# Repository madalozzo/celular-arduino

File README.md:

# celular-arduino

# ATENÇAO - GIP (gambiarra in progress)

Este projeto é um celular básico, do estilo dos Nokia's indestrutíveis do início do século, com a diferença que este não é indestrutível e também não tem o jogo da cobrinha. A idéia é um celular que receba e faça chamadas, receba e envie SMS.

# Peças:

- https://www.adafruit.com/product/1946 
- https://www.arduino.cc/en/pmwiki.php?n=Main/ArduinoBoardProMini de 3v3 8mhz
- https://www.sparkfun.com/products/retired/10968 não está mais a venda mas achei esse substituto: https://www.filipeflop.com/produto/conversor-boost-dc-step-up/
- https://www.filipeflop.com/produto/motor-de-vibracao-1027 o que usei não está mais a venda, este é o mais parecido e tecnicamente é compatível
- Antena GSM (achar o link)
- Alto falante (achar link)
- LCD (achar link tb)
- Bateria (link)
- Microfone (achar link tb...)
- Placa para os botões (projeto eagle neste repo)
- Design do celular (svg no repo tb)

### Desejável
- Espírito gambiarreiro.

# Arduino IDE
Você vai precisar das seguintes libs instaladas:
- Adafruit FONA Library
- Keypad do Mark Stanley
- Lib do LCD deste link https://wiki.seeedstudio.com/I2C_LCD/

# Recursos usados
<div>Icons made by <a href="https://www.flaticon.com/authors/gregor-cresnar" title="Gregor Cresnar">Gregor Cresnar</a> from <a href="https://www.flaticon.com/" title="Flaticon">www.flaticon.com</a></div>

<div>Icons made by <a href="https://www.freepik.com" title="Freepik">Freepik</a> from <a href="https://www.flaticon.com/" title="Flaticon">www.flaticon.com</a></div>

<div>Icons made by <a href="https://www.flaticon.com/authors/those-icons" title="Those Icons">Those Icons</a> from <a href="https://www.flaticon.com/" title="Flaticon">www.flaticon.com</a></div>

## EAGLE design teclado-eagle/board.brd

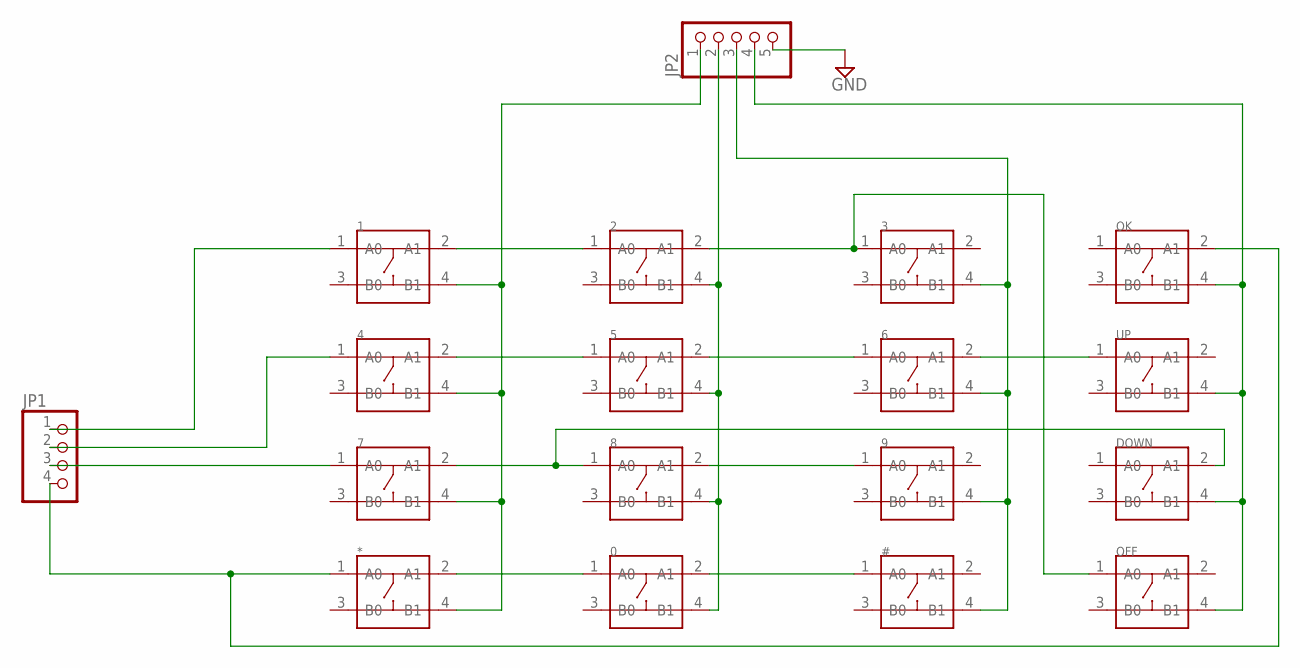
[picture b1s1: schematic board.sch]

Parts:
0, 1, 2, 3, 4, 5, 6, 7, 8, 9: SMD-BUTTON(4P-4.0X4.0X1.7MM)-DHT-1152; SW4-SMD-4.0X4.0X1.7MM
#: SMD-BUTTON(4P-4.0X4.0X1.7MM)-DHT-1152; SW4-SMD-4.0X4.0X1.7MM
*: SMD-BUTTON(4P-4.0X4.0X1.7MM)-DHT-1152; SW4-SMD-4.0X4.0X1.7MM
DOWN: SMD-BUTTON(4P-4.0X4.0X1.7MM)-DHT-1152; SW4-SMD-4.0X4.0X1.7MM
JP1: PINHD-1X4; 1X04
JP2: PINHD-1X5; 1X05
OFF: SMD-BUTTON(4P-4.0X4.0X1.7MM)-DHT-1152; SW4-SMD-4.0X4.0X1.7MM
OK: SMD-BUTTON(4P-4.0X4.0X1.7MM)-DHT-1152; SW4-SMD-4.0X4.0X1.7MM
UP: SMD-BUTTON(4P-4.0X4.0X1.7MM)-DHT-1152; SW4-SMD-4.0X4.0X1.7MM

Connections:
GND: JP2.5
unnamed: 1.2 (A1), 2.1 (A0)
unnamed: 2.2 (A1), 3.1 (A0), OFF.1 (A0)
unnamed: 8.2 (A1), 9.1 (A0)
unnamed: 4.2 (A1), 5.1 (A0)
unnamed: 5.2 (A1), 6.1 (A0)
unnamed: 6.2 (A1), UP.1 (A0)
unnamed: *.1 (A0), JP1.4, OK.2 (A1)
unnamed: 7.2 (A1), 8.1 (A0), DOWN.2 (A1)
unnamed: 0.2 (A1), #.1 (A0)
unnamed: 0.1 (A0), *.2 (A1)
unnamed: 1.4 (B1), 4.4 (B1), 7.4 (B1), *.4 (B1), JP2.1
unnamed: 7.1 (A0), JP1.3
unnamed: 4.1 (A0), JP1.2
unnamed: 1.1 (A0), JP1.1
unnamed: 0.4 (B1), 2.4 (B1), 5.4 (B1), 8.4 (B1), JP2.2
unnamed: 3.4 (B1), 6.4 (B1), 9.4 (B1), #.4 (B1), JP2.3
PLATE: DOWN.4 (B1), JP2.4, OFF.4 (B1), OK.4 (B1), UP.4 (B1)

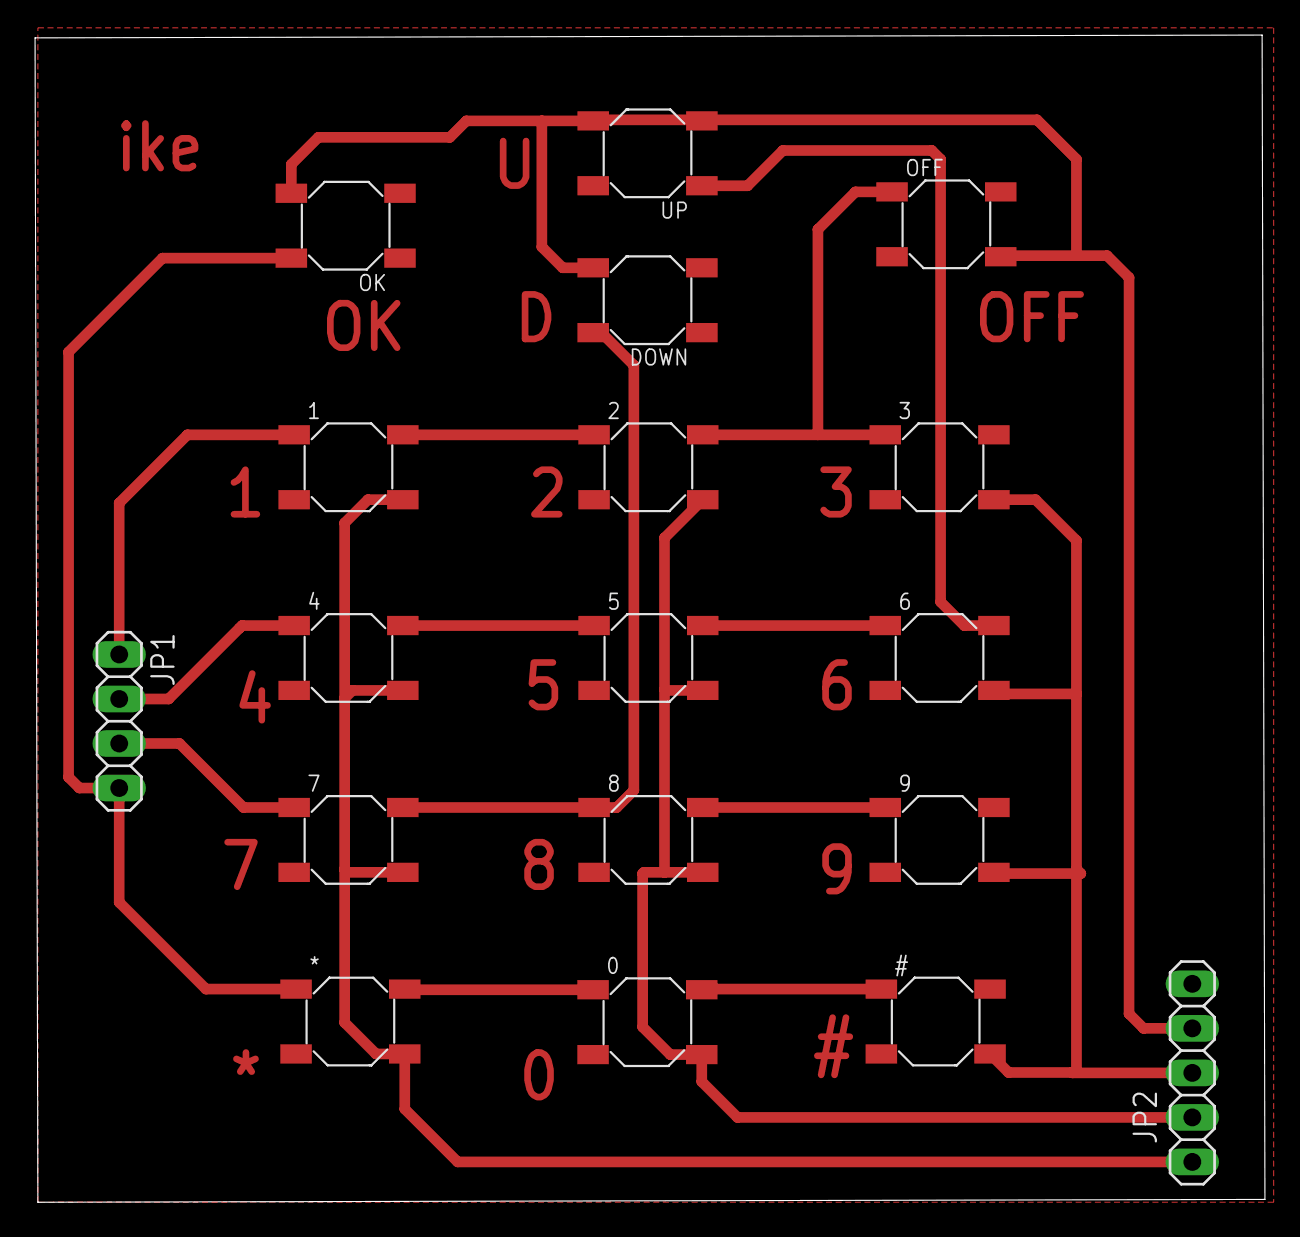
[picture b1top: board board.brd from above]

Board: 2 copper layers, 70.2 x 66.6 mm, 18 parts (0 on the bottom side), 17 nets.

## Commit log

2021-05-24 primeiros testes
2021-05-24 numero de sms, otimizacao de variaveis e desenho de tela
2021-05-27 audio externo e tela de recebendo chamada
2021-05-30 link seedstudio
2021-06-24 diagramas
2021-06-24 placa botoes eagle
2021-06-24 icones
2021-06-24 fritzing
